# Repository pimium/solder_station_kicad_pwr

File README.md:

# solder_station_kicad_pwr
Power supply for the solder station

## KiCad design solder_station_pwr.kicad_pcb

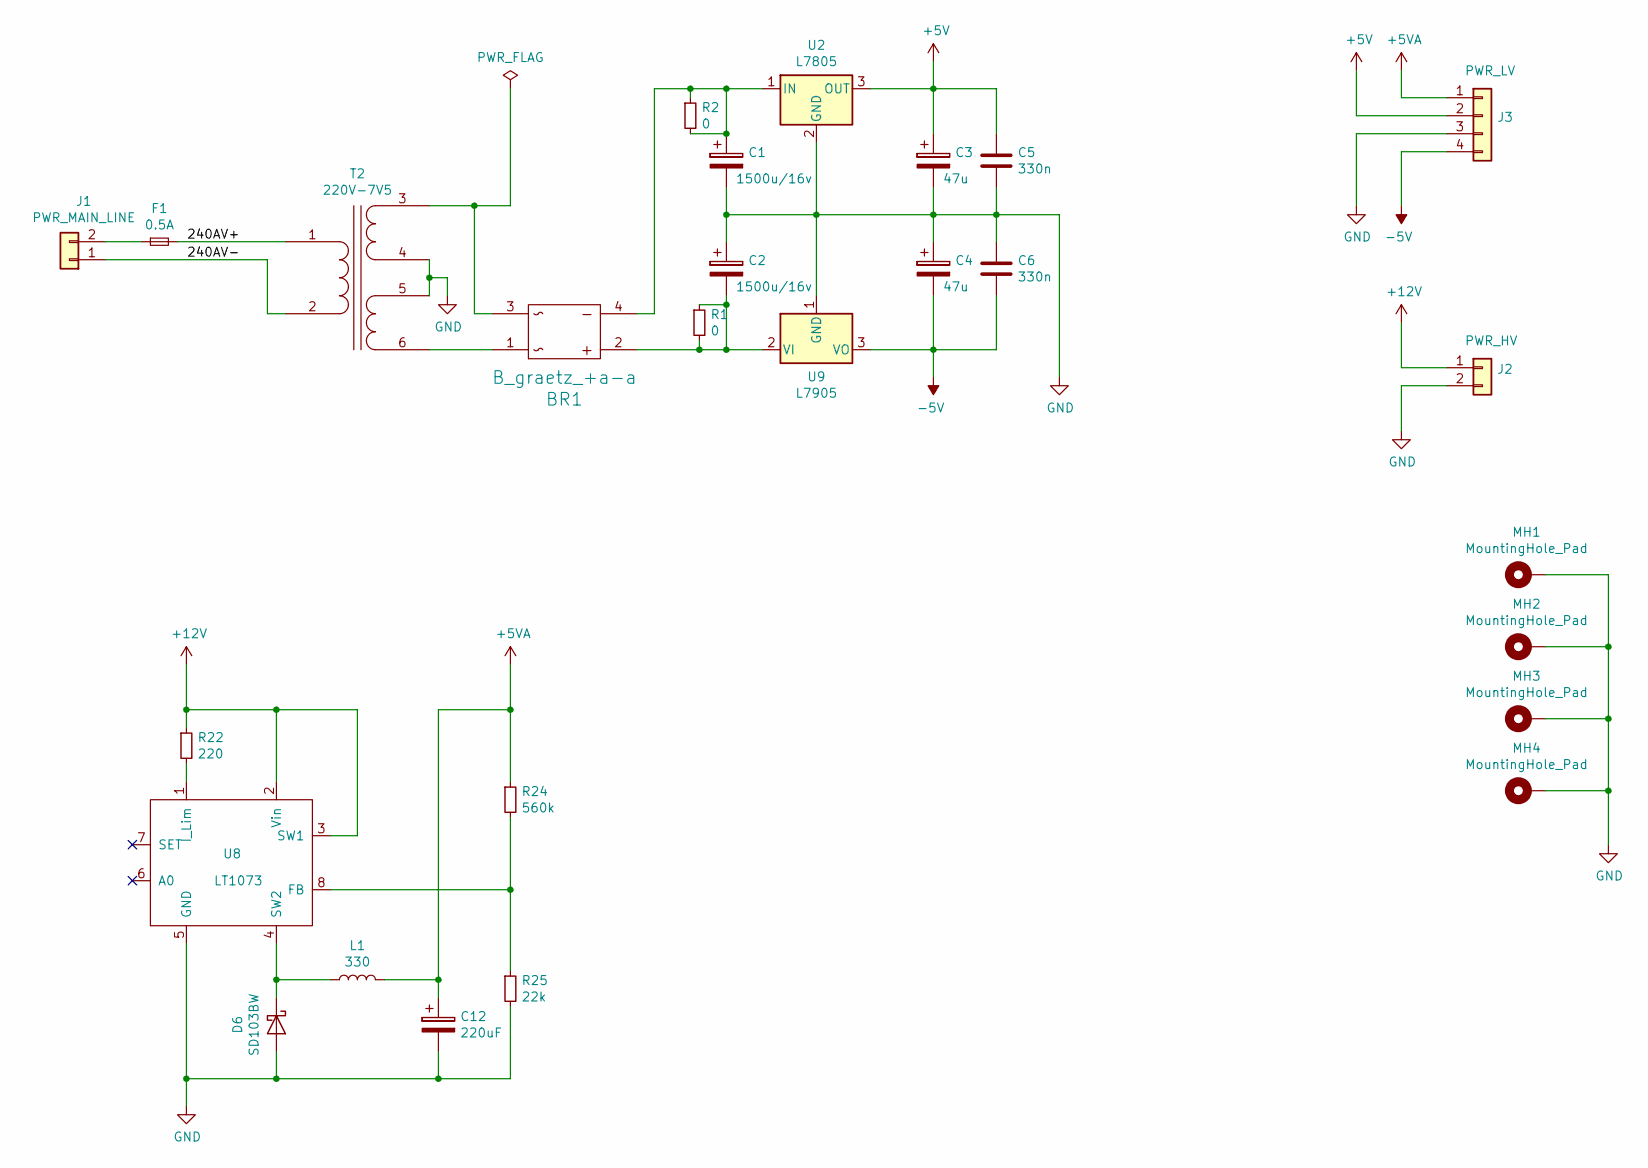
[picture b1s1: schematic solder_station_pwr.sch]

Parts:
BR1: B_graetz_+a-a; Diode_Bridge_Round_D9.8mm
C1, C2: 1500u/16v; CP_Radial_D10.0mm_P5.00mm
C3, C4: 47u; CP_Radial_D5.0mm_P2.50mm
C5, C6: 330n; C_0805_2012Metric_Pad1.15x1.40mm_HandSolder
C12: 220uF; CP_Radial_D10.0mm_P5.00mm
D6: SD103BW; D_SOD-123
F1: 0.5A; Fuseholder_Cylinder-5x20mm_Schurter_0031_8201_Horizontal_Op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
J1: PWR_MAIN_LINE; SolderWirePad_1x02_P5.08mm_Drill1.5mm
J2: PWR_HV; SolderWirePad_1x02_P5.08mm_Drill1.5mm
J3: PWR_LV; PinSocket_1x04_P2.54mm_Vertical
L1: 330; L_Taiyo-Yuden_NR-80xx_HandSoldering
MH1, MH2, MH3, MH4: MountingHole_Pad; MountingHole_3.2mm_M3_Pad
R1, R2: 0; R_1206_3216Metric_Pad1.42x1.75mm_HandSolder
R22: 220; R_0805_2012Metric_Pad1.15x1.40mm_HandSolder
R24: 560k; R_0805_2012Metric_Pad1.15x1.40mm_HandSolder
R25: 22k; R_0805_2012Metric_Pad1.15x1.40mm_HandSolder
T2: 220V-7V5; Trafo_Conrad
U2: L7805; TO-220-3_Vertical
U8: LT1073; SOIC-8_3.9x4.9mm_P1.27mm
U9: L7905; TO-220-3_Vertical

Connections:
+5V: C3.1, C5.1, J3.2, U2.3 (OUT)
+5VA: C12.1, J3.1, L1.2, R24.1
+12V: J2.1, R22.1, U8.2 (Vin), U8.3 (SW1)
-5V: C4.2, C6.2, J3.4, U9.3 (VO)
/240AV+: F1.2, T2.1 (AA)
/240AV-: J1.1, T2.2 (AB)
GND: C1.2, C2.1, C3.2, C4.1, C5.2, C6.1, C12.2, D6.2 (A), J2.2, J3.3, MH1.1, MH2.1, MH3.1, MH4.1, R25.2, T2.4 (SB), T2.5 (SC), U2.2 (GND), U8.5 (GND), U9.1 (GND)
unnamed: BR1.1, T2.6 (SD)
unnamed: BR1.2, C2.2, R1.1, R1.2, U9.2 (VI)
unnamed: BR1.3, T2.3 (SA)
unnamed: BR1.4, C1.1, R2.1, R2.2, U2.1 (IN)
unnamed: D6.1 (K), L1.1, U8.4 (SW2)
unnamed: F1.1, J1.2
unnamed: R22.2, U8.1 (I_Lim)
unnamed: R24.2, R25.1, U8.8 (FB)

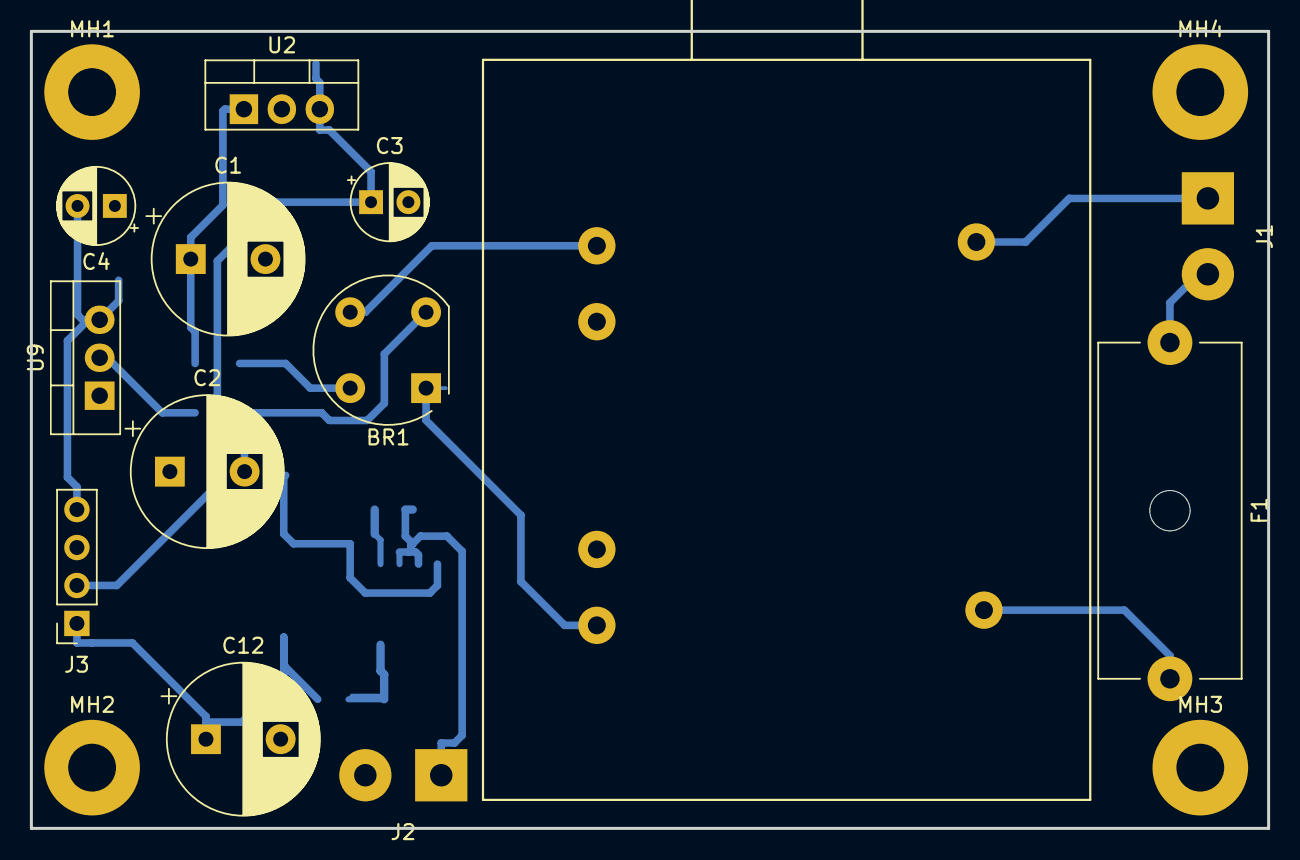
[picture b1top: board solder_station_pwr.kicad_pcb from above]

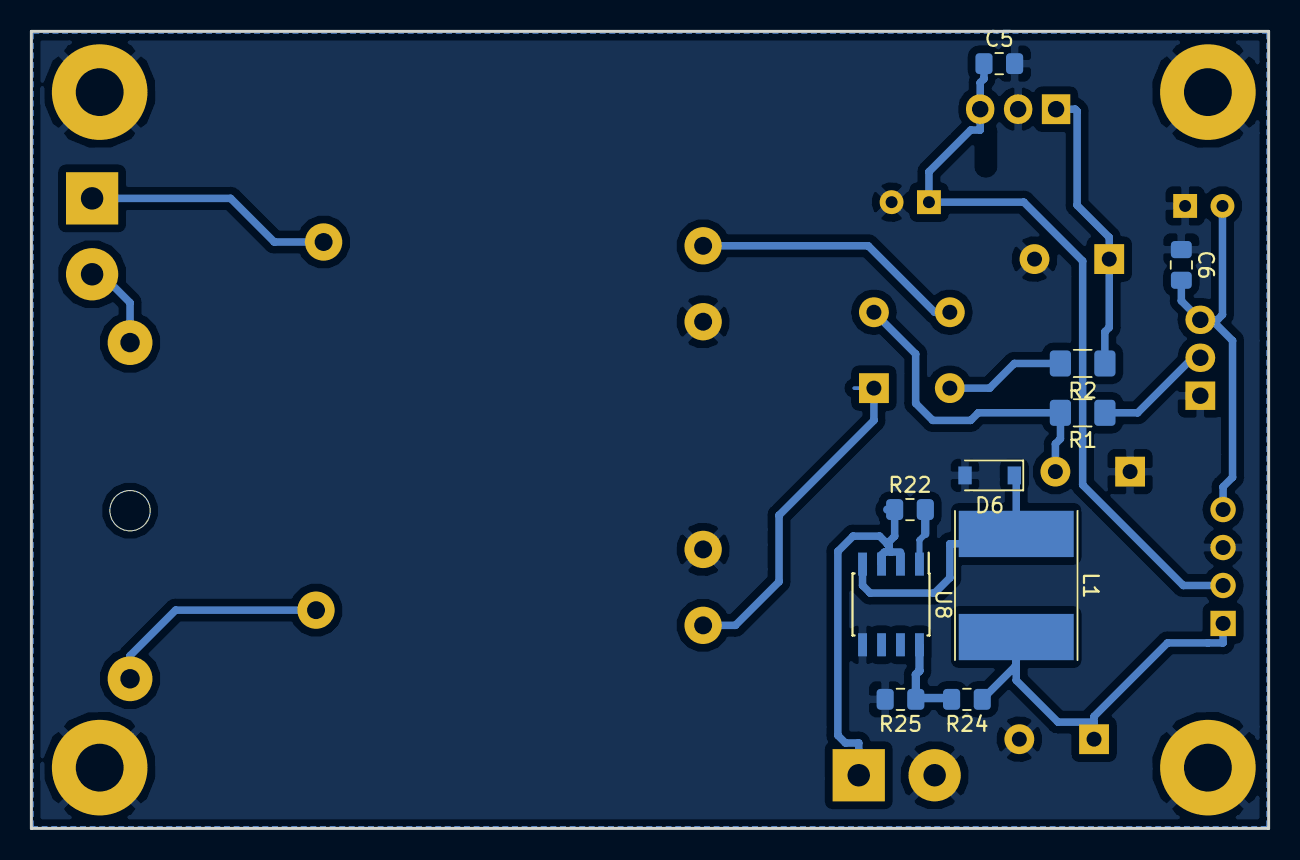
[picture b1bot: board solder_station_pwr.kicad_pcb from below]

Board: 2 copper layers, 82.8 x 53.3 mm, 27 parts (10 on the bottom side), 15 nets.

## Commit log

2018-06-20 start filament heater
2018-07-13 push pull
2018-08-18 Create a board just for the power supply and filament heating
2018-09-29 add attribute file and remove date from pro file
2018-10-14 add darligton stage instead of simple transitor
2018-11-18 remove ne555, using the atmega pwm OC0B to control the transistor
2018-11-18 schematic done
2018-11-21 add lm4871 as filament heater
2018-11-25 version
2019-04-17 Add power suppply has now just 2 differents 5 volt and a -5 volt
